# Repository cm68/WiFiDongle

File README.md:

# WiFiDongle
WiFi to serial server for ESP32 with OLED display support.

See https://www.zen-room.org/the-zen-room/serial-to-wifi-plug

## Hardware

- ESP32 dev board
- Optional: SSD1306 or SH1107 128x32 or 128x64 OLED display (I2C, address 0x3C)

## Prerequisites

### PlatformIO (recommended)

Install PlatformIO Core (CLI):

```sh
pip install platformio
```

Or install the VS Code extension: search for "PlatformIO IDE" in the extensions marketplace.

### arduino-cli (alternative)

Install arduino-cli:

```sh
curl -fsSL https://raw.githubusercontent.com/arduino/arduino-cli/master/install.sh | sh
```

Then install the ESP32 board support:

```sh
arduino-cli core update-index
arduino-cli core install esp32:esp32
```

## Building

### With PlatformIO (default)

```sh
make              # compile
make upload       # compile and flash to ESP32
make monitor      # open serial monitor
make upload-monitor  # flash then monitor
make clean        # clean build artifacts
```

### With arduino-cli

```sh
make ino              # compile
make ino-upload       # compile and flash to ESP32
make ino-upload-monitor  # flash then monitor
make ino-clean        # clean build artifacts
```

### Options

Override the serial port or baud rate:

```sh
make upload PORT=/dev/ttyACM0
make monitor BAUD=38400
```

## Configuration

On first boot, the device uses default credentials defined in the source
(`DEFAULT_SSID`, `DEFAULT_PASS`, etc. in `WiFiDongle.ino`).

At runtime, send any character over the serial console to enter the
configuration editor. Changes are saved to EEPROM and persist across reboots.
If WiFi fails to connect within 30 seconds, the editor opens automatically.

### EEPROM format

The EEPROM stores a single ASCII string:

```
"ssid","password",port:baud:flowctl:rx,tx,rts,cts:displayht:displaydrv
```

| Field      | Description                          | Default |
|------------|--------------------------------------|---------|
| ssid       | WiFi network name                    | yourssid |
| password   | WiFi password                        | yourpassword |
| port       | TCP port for the telnet server       | 23      |
| baud       | UART baud rate for Serial2           | 38400   |
| flowctl    | Hardware flow control (0=off, 1=RTS/CTS) | 0   |
| rx         | Serial2 RX GPIO pin                  | 17      |
| tx         | Serial2 TX GPIO pin                  | 16      |
| rts        | Serial2 RTS GPIO pin                 | 5       |
| cts        | Serial2 CTS GPIO pin                 | 4       |
| displayht  | OLED display height (32 or 64)       | 32      |
| displaydrv | Display driver (0=SSD1306, 1=SH1107) | 0       |

The format is backward compatible: if older fields are present without the
newer ones (flowctl, pins), defaults are filled in and written back to EEPROM
automatically on boot.

## Custom font

`FreeSans8pt7b.h` was generated from the GNU FreeSans TrueType font using
the Adafruit GFX `fontconvert` tool:

```sh
cd /path/to/Adafruit_GFX_Library/fontconvert
make
./fontconvert /usr/share/fonts/truetype/freefont/FreeSans.ttf 8 > FreeSans8pt7b.h
```

The `fontconvert` source is included in the
[Adafruit GFX Library](https://github.com/adafruit/Adafruit-GFX-Library/tree/master/fontconvert).
It requires the FreeType development library (`libfreetype-dev` on Debian/Ubuntu).

## RS-232 connector and signal direction

The PCB is designed to be stuffed with a **female DB connector**, making the
board a DCE (Data Communications Equipment). This is correct for a device
that is connected to by a DTE (e.g. a PC with a male connector).

A DCE drives two signals:

| Signal | Direction | Description |
|--------|-----------|-------------|
| TXD    | DCE → DTE | Data output (ESP32 TX → connector pin 2) |
| CTS    | DCE → DTE | Clear to send (ESP32 RTS → connector pin 8) |

And receives two signals:

| Signal | Direction | Description |
|--------|-----------|-------------|
| RXD    | DTE → DCE | Data input (connector pin 3 → ESP32 RX) |
| RTS    | DTE → DCE | Request to send (connector pin 7 → ESP32 CTS) |

Note that the ESP32's RTS output maps to the connector's CTS pin, and the
ESP32's CTS input maps to the connector's RTS pin — the signal names cross
over at the DTE/DCE boundary.

**Important:** If the board is stuffed with a male connector instead, the
TXD/RXD and RTS/CTS pairs will be reversed, since a male connector implies
DTE pinout. The board would then drive the wrong pins.

When hardware flow control is disabled, the ESP32 asserts (drives low) the
RTS pin so that a connected DTE always sees CTS active.

At boot, CTS is held inactive (disasserted) until WiFi connects, then
asserted. This prevents the DTE from sending data before the network is
ready, and also serves as a quick visual check with an RS-232 monitor that
the CTS signal path is working.

## PCB design

The `kicad/` directory contains the KiCad schematic and PCB layout for a
carrier board. It includes a custom ESP32 DevKit V1 footprint and symbol
library. Open `kicad/WiFiDongle.kicad_pro` in KiCad 8 to view or edit.

## Display pin order

Many displays are compatible with the 4-pin header, but some have a different
arrangement of the power pins. The PCB implements the most common pin order:
GND, VCC, SCLK, SDATA. However, one family of 128x64 boards uses VCC, GND,
SCLK, SDATA. This can be corrected by cutting the circuit board traces and
using magnet wire or wire wrap wire to reorder the pins.

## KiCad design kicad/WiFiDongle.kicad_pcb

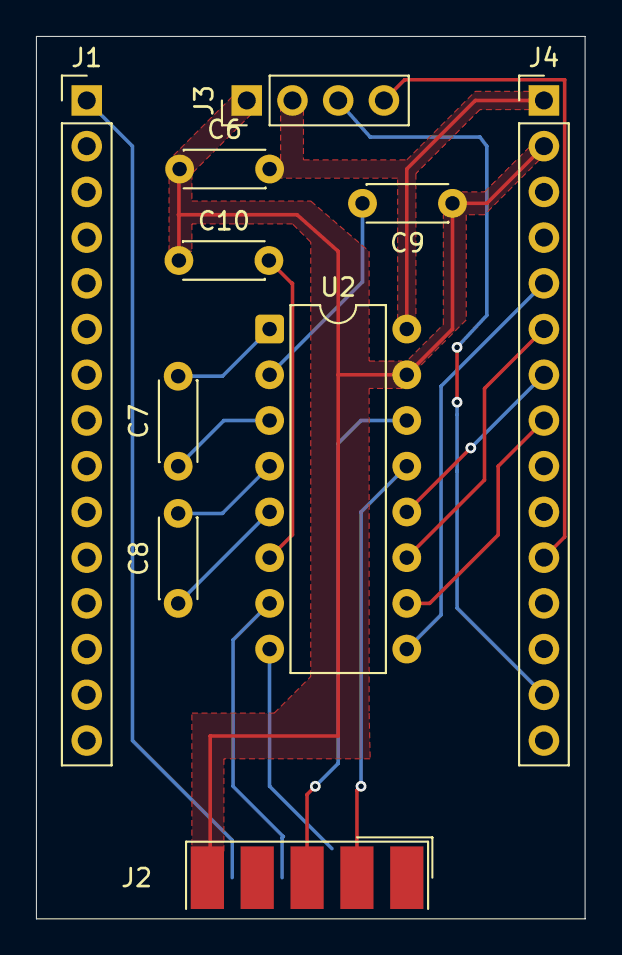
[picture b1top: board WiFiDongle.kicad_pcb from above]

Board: 2 copper layers, 30.5 x 49.0 mm, 10 parts (0 on the bottom side), 18 nets.

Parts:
C6, C7, C8, C9, C10: 100nF; C_Disc_D4.3mm_W1.9mm_P5.00mm
J1, J4: Conn_01x15; PinHeader_1x15_P2.54mm_Vertical
J2: DB9-Edgemount; DSUB-9_Socket_EdgeMount_P2.77mm
J3: Conn_01x04; PinHeader_1x04_P2.54mm_Vertical
U2: MAX3232; DIP-16_W7.62mm

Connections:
+3.3V: C6.2, J3.2, J4.1, U2.16 (VCC)
/RS232_CTS: J2.7, U2.8 (R2IN)
/RS232_RTS: J2.8, U2.7 (T2OUT)
/RS232_RX: J2.2, U2.13 (R1IN)
/RS232_TX: J2.3, U2.14 (T1OUT)
/UART_RX: J4.7, U2.12 (R1OUT)
/UART_TX: J4.6, U2.11 (T1IN)
GND: C6.1, C9.1, C10.1, J2.5, J3.1, J4.2, U2.15 (GND)
unnamed: J3.3, J4.14
unnamed: J3.4, J4.11
unnamed: J4.5, U2.9 (R2OUT)
unnamed: J4.8, U2.10 (T2IN)
unnamed: C7.2, U2.1 (C1+)
unnamed: C7.1, U2.3 (C1-)
unnamed: C8.2, U2.4 (C2+)
unnamed: C8.1, U2.5 (C2-)
unnamed: C9.2, U2.2 (VS+)
unnamed: C10.2, U2.6 (VS-)

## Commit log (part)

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2023-06-13 added source code
2026-03-04 added schematic
